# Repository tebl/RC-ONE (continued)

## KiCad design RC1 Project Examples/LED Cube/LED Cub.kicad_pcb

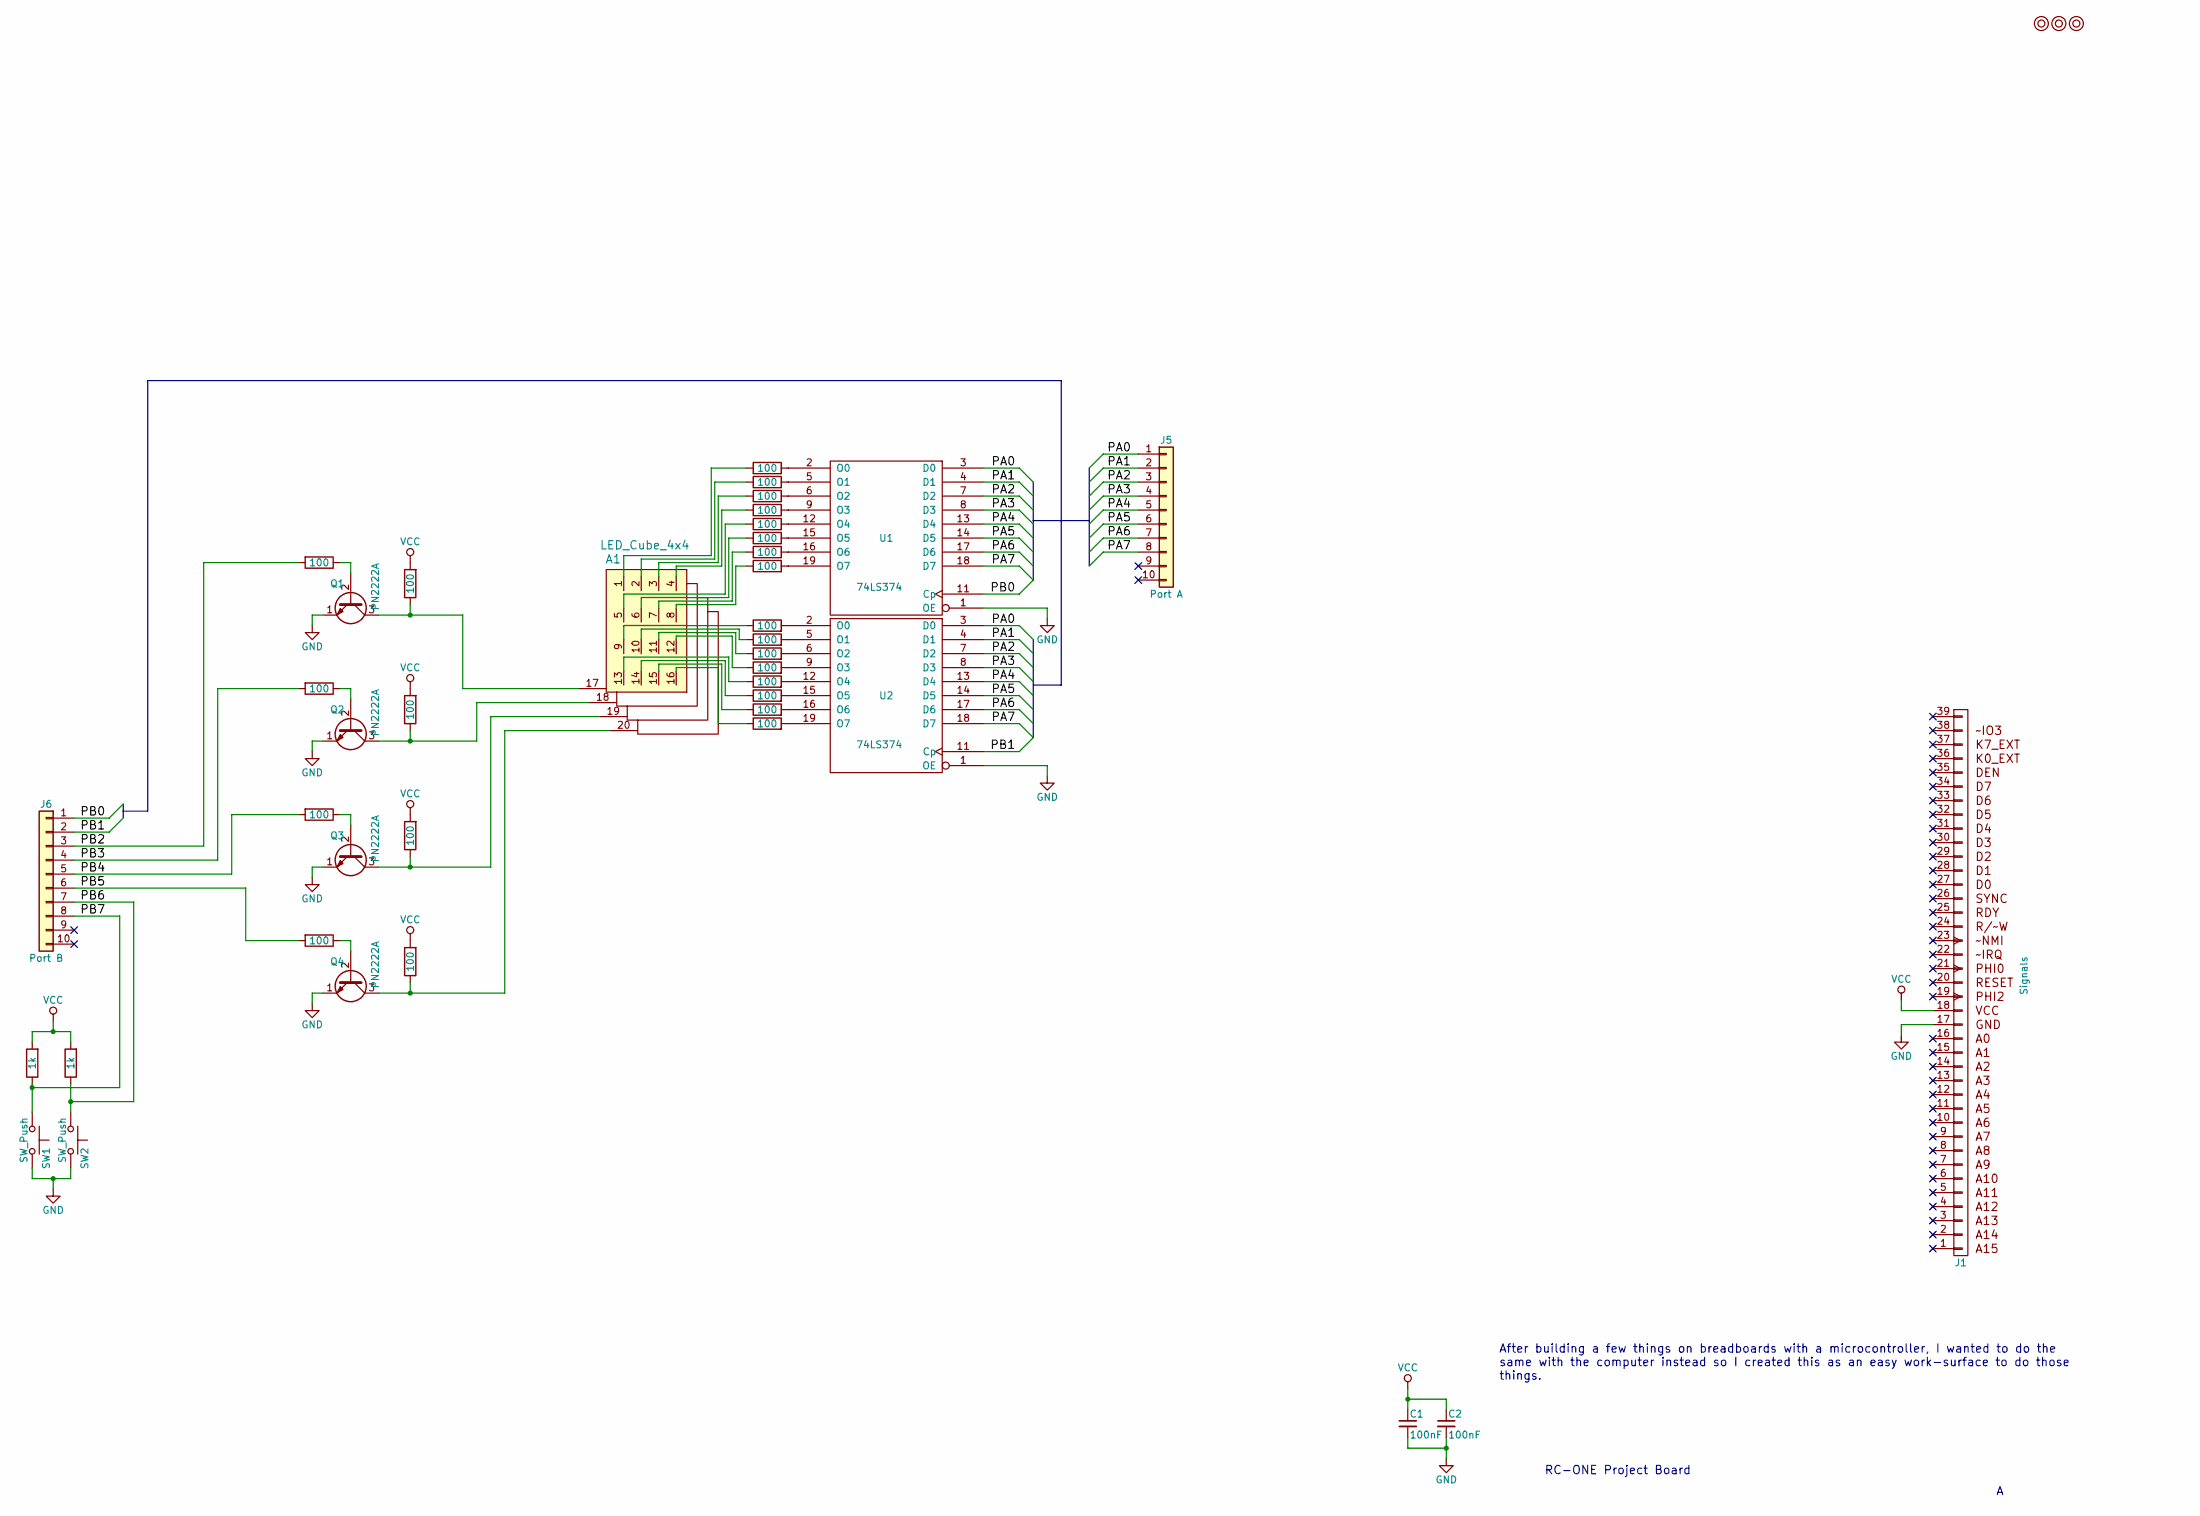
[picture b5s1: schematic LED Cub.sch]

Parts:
A1: LED_Cube_4x4
C1, C2: 100nF; C_Disc_D4.7mm_W2.5mm_P5.00mm
J1: Signals; Pin_Header_Straight_1x39_Pitch2.54mm
J5: Port A; Pin_Header_Straight_1x10_Pitch2.54mm
J6: Port B; Pin_Header_Straight_1x10_Pitch2.54mm
M1, M2, M3: Mounting; 1pin
Q1, Q2, Q3, Q4: PN2222A; TO-92_Molded_Narrow
R1, R2, R3, R4, R5, R6, R7, R8, R9, R10, R11, R12, R15, R16, R17, R18, R19, R20, R21, R22, R23, R24, R25, R26: 100; R_Axial_DIN0207_L6.3mm_D2.5mm_P10.16mm_Horizontal
R13, R14: 1k; R_Axial_DIN0207_L6.3mm_D2.5mm_P10.16mm_Horizontal
SW1, SW2: SW_Push; SW_PUSH_6mm
U1, U2: 74LS374; DIP-20_W7.62mm_Socket_LongPads

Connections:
/PA0: J5.1, U1.3 (D0), U2.3 (D0)
/PA1: J5.2, U1.4 (D1), U2.4 (D1)
/PA2: J5.3, U1.7 (D2), U2.7 (D2)
/PA3: J5.4, U1.8 (D3), U2.8 (D3)
/PA4: J5.5, U1.13 (D4), U2.13 (D4)
/PA5: J5.6, U1.14 (D5), U2.14 (D5)
/PA6: J5.7, U1.17 (D6), U2.17 (D6)
/PA7: J5.8, U1.18 (D7), U2.18 (D7)
/PB0: J6.1, U1.11 (Cp)
/PB1: J6.2, U2.11 (Cp)
/PB2: J6.3, R1.2
/PB3: J6.4, R2.2
/PB4: J6.5, R3.2
/PB5: J6.6, R4.2
/PB6: J6.7, R14.1, SW2.1
/PB7: J6.8, R13.1, SW1.1
GND: C1.2, C2.2, J1.17, Q1.1 (E), Q2.1 (E), Q3.1 (E), Q4.1 (E), SW1.2, SW2.2, U1.1 (OE), U1.10 (GND), U2.1 (OE), U2.10 (GND)
unnamed: A1.1 (la1), R8.1
unnamed: A1.2 (la2), R10.1
unnamed: A1.3 (la3), R11.1
unnamed: A1.4 (la4), R12.1
unnamed: A1.5 (la5), R15.1
unnamed: A1.6 (la6), R16.1
unnamed: A1.7 (la7), R17.1
unnamed: A1.8 (la8), R18.1
unnamed: A1.9 (la9), R19.1
unnamed: A1.10 (la10), R20.1
unnamed: A1.11 (la11), R21.1
unnamed: A1.12 (la12), R22.1
unnamed: A1.13 (la13), R23.1
unnamed: A1.14 (la14), R24.1
unnamed: A1.15 (la15), R25.1
unnamed: A1.16 (la16), R26.1
unnamed: A1.17 (layer0), Q1.3 (C), R9.1
unnamed: A1.18 (layer1), Q2.3 (C), R5.1
unnamed: A1.19 (layer2), Q3.3 (C), R6.1
unnamed: A1.20 (layer3), Q4.3 (C), R7.1
unnamed: Q1.2 (B), R1.1
unnamed: Q2.2 (B), R2.1
unnamed: Q3.2 (B), R3.1
unnamed: Q4.2 (B), R4.1
unnamed: R8.2, U1.2 (O0)
unnamed: R10.2, U1.5 (O1)
unnamed: R11.2, U1.6 (O2)
unnamed: R12.2, U1.9 (O3)
unnamed: R15.2, U1.12 (O4)
unnamed: R16.2, U1.15 (O5)
unnamed: R17.2, U1.16 (O6)
unnamed: R18.2, U1.19 (O7)
unnamed: R19.2, U2.2 (O0)
unnamed: R20.2, U2.5 (O1)
unnamed: R21.2, U2.6 (O2)
unnamed: R22.2, U2.9 (O3)
unnamed: R23.2, U2.12 (O4)
unnamed: R24.2, U2.15 (O5)
unnamed: R25.2, U2.16 (O6)
unnamed: R26.2, U2.19 (O7)
VCC: C1.1, C2.1, J1.18, R5.2, R6.2, R7.2, R9.2, R13.2, R14.2, U1.20 (VCC), U2.20 (VCC)

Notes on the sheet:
RC-ONE Project Board
After building a few things on breadboards with a microcontroller, I wanted to do the same with the computer instead so I created this as an easy work-surface to do those things.

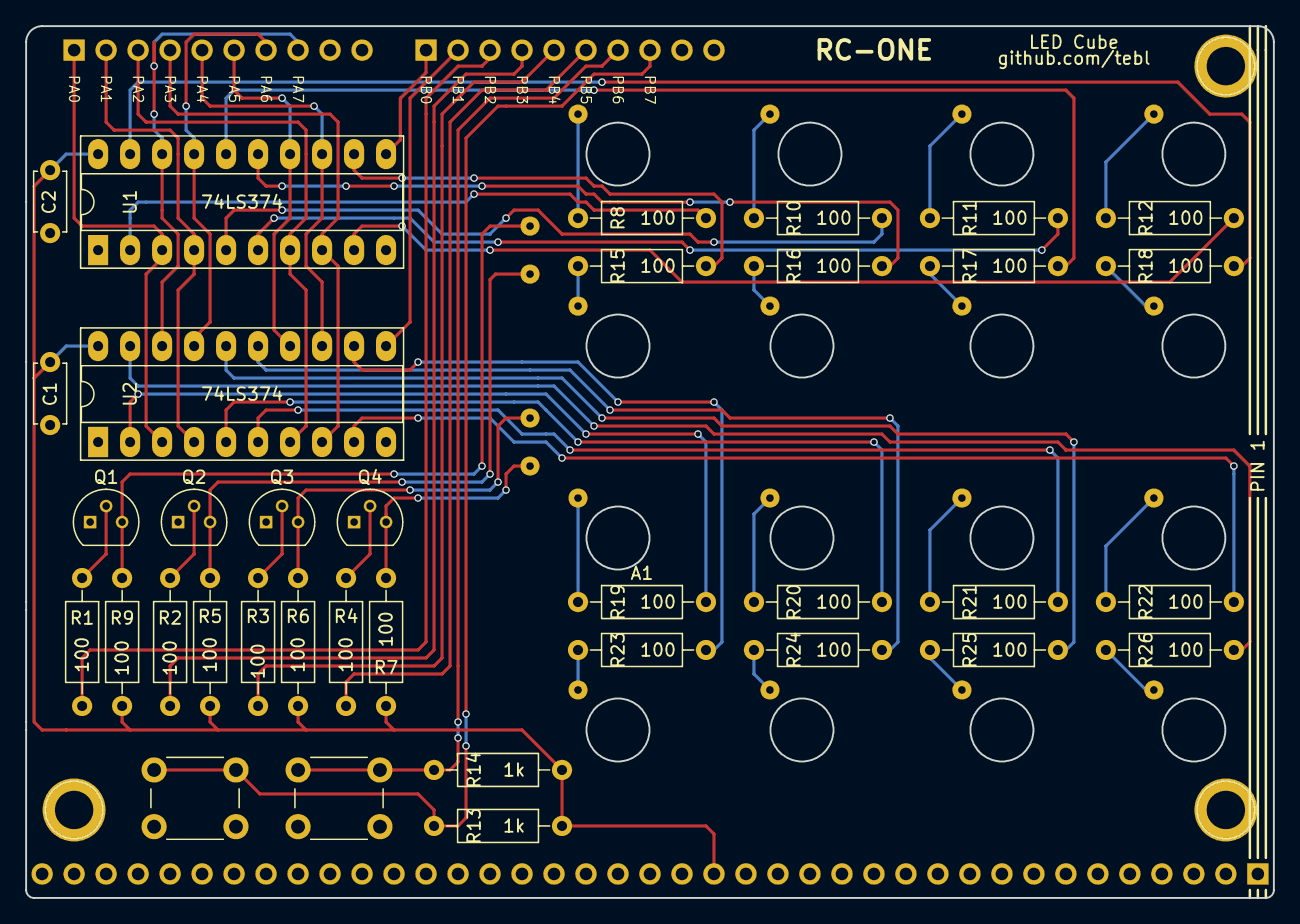
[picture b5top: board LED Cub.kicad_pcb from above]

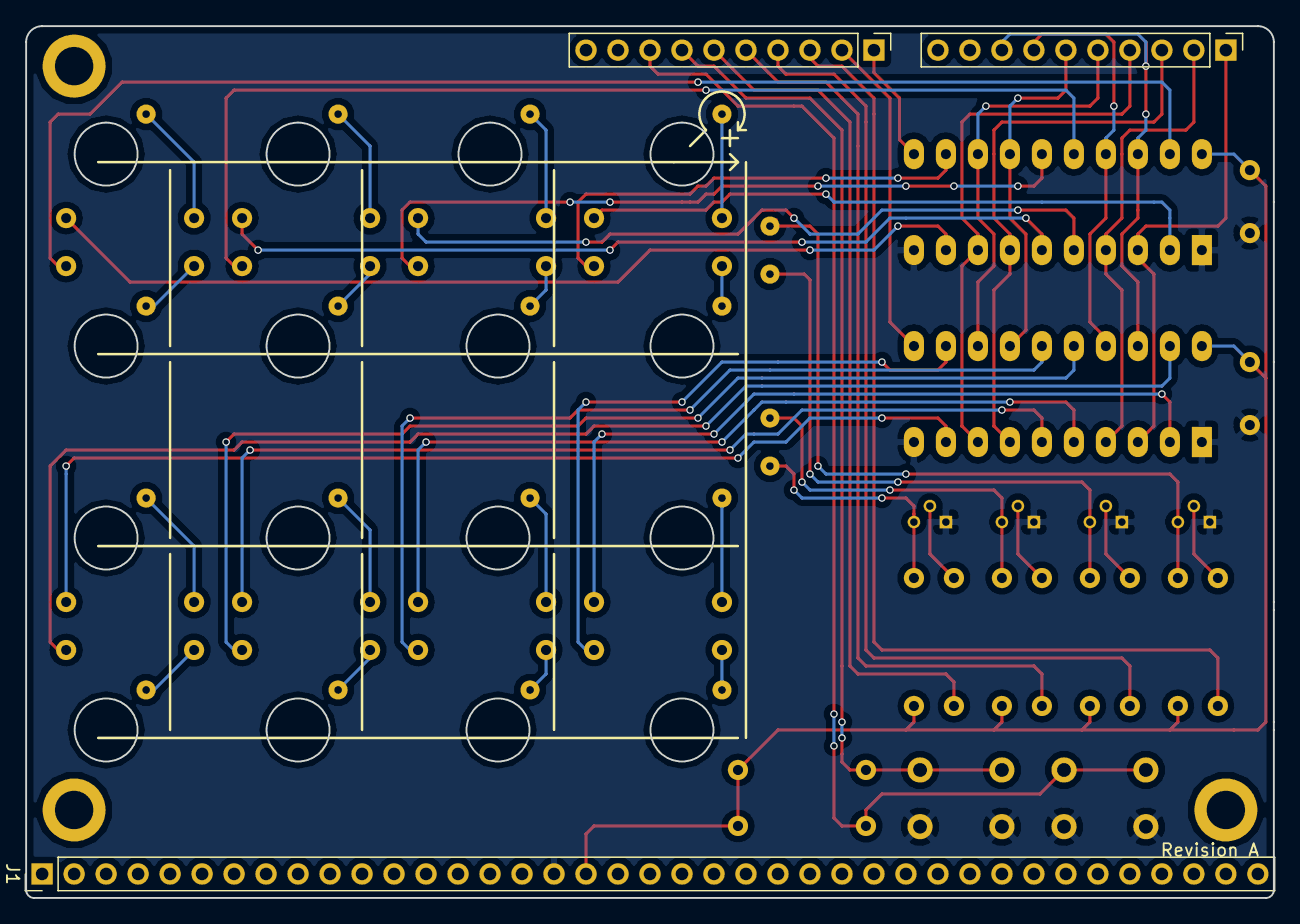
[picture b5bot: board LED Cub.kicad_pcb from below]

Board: 2 copper layers, 99.1 x 69.2 mm, 43 parts (3 on the bottom side), 58 nets.

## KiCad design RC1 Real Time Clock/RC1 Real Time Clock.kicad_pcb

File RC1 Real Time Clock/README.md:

# RC-ONE Real Time Clock (RTC)

**This design is untested!**

Wanted a Real Time Clock, but have been a hard time locating a suitable circuit for it since most of them either contain batteries that ran out a decade ago or are based on I2C or SPI (which I don't feel like bit-banging now or possibly ever). Appearantly there is a chip called DS12885 that is suitable and was readily used on the XT and AT line of computers, so they are cheap and plentiful though have a multi-plexed bus that is probably why it haven't been much used for SBC builds. Did however find an article in [Elektor Electronics from april 1985](https://www.americanradiohistory.com/UK/Elektor/80s/Elektor-1985-04.pdf) that uses it, so I've tried my best to adapt it for use here.

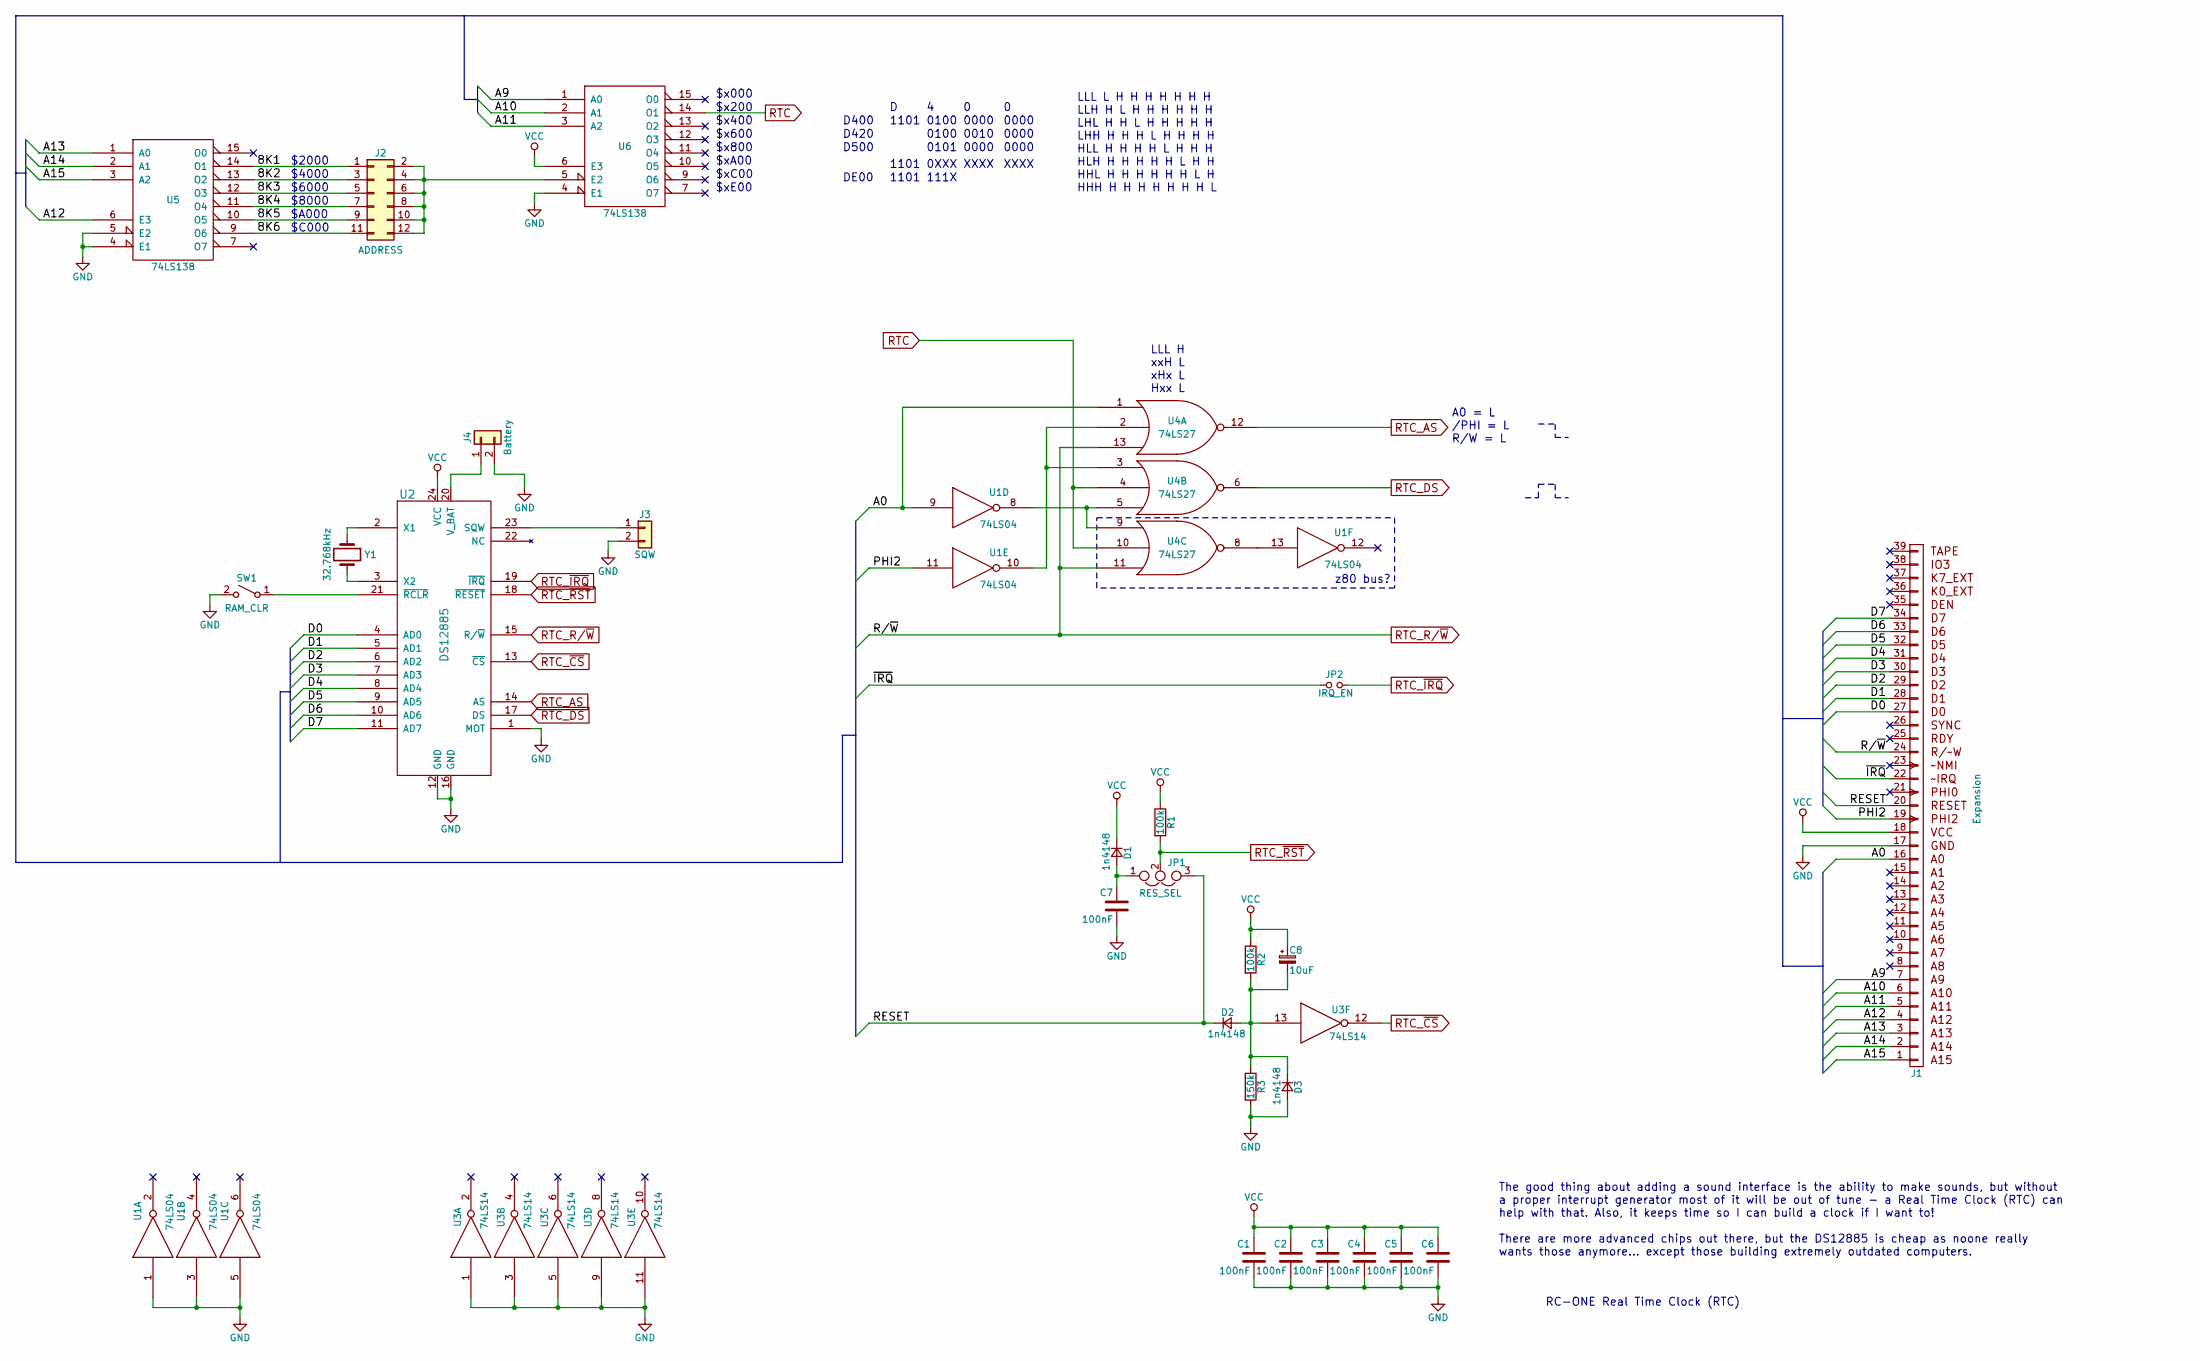
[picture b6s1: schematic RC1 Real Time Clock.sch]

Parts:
C1, C2, C3, C4, C5, C6, C7: 100nF; C_Disc_D4.7mm_W2.5mm_P5.00mm
C8: 10uF; CP_Radial_D5.0mm_P2.50mm
D1, D2, D3: 1n4148; D_DO-35_SOD27_P7.62mm_Horizontal
J1: Expansion; Pin_Header_Angled_1x39_Pitch2.54mm
J2: ADDRESS; Pin_Header_Straight_2x06_Pitch2.54mm
J3: SQW; Pin_Header_Straight_1x02_Pitch2.54mm
J4: Battery; Pin_Header_Straight_1x02_Pitch2.54mm
JP1: RES_SEL; Pin_Header_Straight_1x03_Pitch2.54mm
JP2: IRQ_EN; Pin_Header_Straight_1x02_Pitch2.54mm
R1, R2: 100k; R_Axial_DIN0207_L6.3mm_D2.5mm_P10.16mm_Horizontal
R3: 150k; R_Axial_DIN0207_L6.3mm_D2.5mm_P10.16mm_Horizontal
SW1: RAM_CLR; SW_PUSH_6mm
U1: 74LS04; DIP-14_W7.62mm_Socket
U2: DS12885; DIP-24_W15.24mm_Socket
U3: 74LS14; DIP-14_W7.62mm_Socket
U4: 74LS27; DIP-14_W7.62mm_Socket
U5, U6: 74LS138; DIP-16_W7.62mm_Socket
Y1: 32.768kHz; Crystal_HC49-U_Vertical

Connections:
/8K1: J2.1, U5.14 (O1)
/8K2: J2.3, U5.13 (O2)
/8K3: J2.5, U5.12 (O3)
/8K4: J2.7, U5.11 (O4)
/8K5: J2.9, U5.10 (O5)
/8K6: J2.11, U5.9 (O6)
/A0: J1.16 (A0), U1.9, U4.1
/A9: J1.7 (A9), U6.1 (A0)
/A10: J1.6 (A10), U6.2 (A1)
/A11: J1.5 (A11), U6.3 (A2)
/A12: J1.4 (A12), U5.6 (E3)
/A13: J1.3 (A13), U5.1 (A0)
/A14: J1.2 (A14), U5.2 (A1)
/A15: J1.1 (A15), U5.3 (A2)
/D0: J1.27 (D0), U2.4 (AD0)
/D1: J1.28 (D1), U2.5 (AD1)
/D2: J1.29 (D2), U2.6 (AD2)
/D3: J1.30 (D3), U2.7 (AD3)
/D4: J1.31 (D4), U2.8 (AD4)
/D5: J1.32 (D5), U2.9 (AD5)
/D6: J1.33 (D6), U2.10 (AD6)
/D7: J1.34 (D7), U2.11 (AD7)
/PHI2: J1.19 (PHI2), U1.11
/RESET: D2.1 (K), J1.20 (RESET), JP1.3
/~IRQ: J1.22 (IRQ), JP2.1
GND: C1.2, C2.2, C3.2, C4.2, C5.2, C6.2, C7.2, D3.2 (A), J1.17, J3.2, J4.2, R3.2, SW1.2 (B), U1.1, U1.3, U1.5, U1.7 (GND), U2.1 (MOT), U2.12 (GND), U2.16 (GND), U3.1, U3.3, U3.5, U3.7 (GND), U3.9, U3.11, U4.7 (GND), U5.4 (E1), U5.5 (E2), U5.8 (GND), U6.4 (E1), U6.8 (GND)
unnamed: C7.1, D1.2 (A), JP1.1
unnamed: C8.2, D2.2 (A), D3.1 (K), R2.2, R3.1, U3.13
unnamed: J2.2, J2.4, J2.6, J2.8, J2.10, J2.12, U6.5 (E2)
unnamed: J3.1, U2.23 (SQW)
unnamed: J4.1, U2.20 (V_BAT)
unnamed: SW1.1 (A), U2.21 (~RCLR)
unnamed: U1.8, U4.5, U4.9
unnamed: U1.10, U4.2, U4.3
unnamed: U1.13, U4.8
unnamed: U2.2 (X1), Y1.1
unnamed: U2.3 (X2), Y1.2
RTC: U4.4, U4.10, U6.14 (O1)
RTC_AS: U2.14 (AS), U4.12
RTC_DS: U2.17 (DS), U4.6
RTC_R/~W: J1.24 (RW), U2.15 (R/~W), U4.11, U4.13
RTC_~CS: U2.13 (~CS), U3.12
RTC_~IRQ: JP2.2, U2.19 (~IRQ)
RTC_~RST: JP1.2, R1.2, U2.18 (~RESET)
VCC: C1.1, C2.1, C3.1, C4.1, C5.1, C6.1, C8.1, D1.1 (K), J1.18, R1.1, R2.1, U1.14 (VCC), U2.24 (VCC), U3.14 (VCC), U4.14 (VCC), U5.16 (VCC), U6.6 (E3), U6.16 (VCC)

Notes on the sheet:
RC-ONE Real Time Clock (RTC)
$2000
$4000
$6000
$8000
$A000
$C000
$x000
1101
0100
0010
0000
0101
D420
D400
D500
LLL L H H H H H H H LLH H L H H H H H H LHL H H L H H H H H LHH H H H L H H H H HLL H H H H L H H H HLH H H H H H L H H HHL H H H H H H L H HHH H H H H H H H L
0XXX
XXXX
DE00
111X
$x200
$x600
$x800
$xC00
$xA00
The good thing about adding a sound interface is the ability to make sounds, but without a proper interrupt generator most of it will be out of tune - a Real Time Clock (RTC) can help with that. Also, it keeps time so I can build a clock if I want to! There are more advanced chips out there, but th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
$xE00
$x400
LLL H xxH L xHx L Hxx L
A0 = L /PHI = L R/W = L
z80 bus?

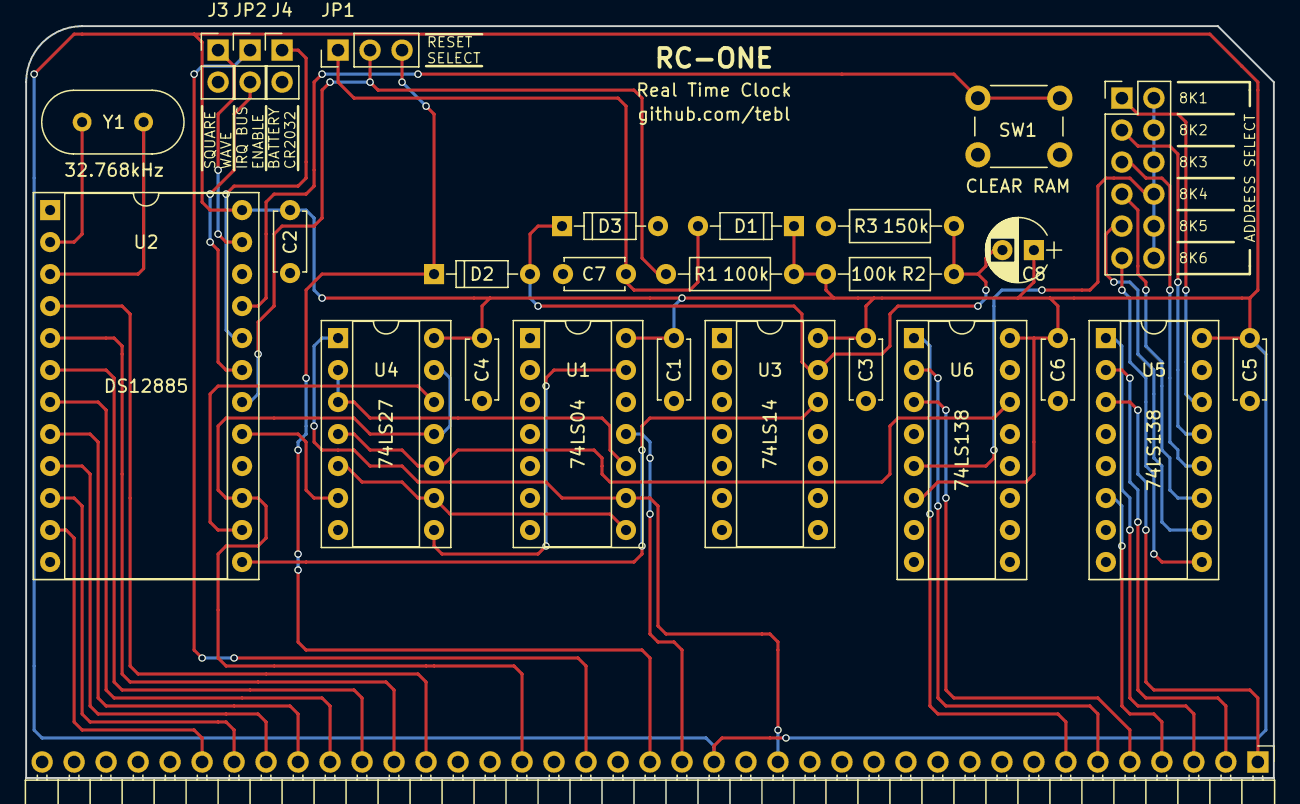
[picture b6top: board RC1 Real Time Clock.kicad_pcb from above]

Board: 2 copper layers, 99.1 x 59.7 mm, 28 parts (0 on the bottom side), 45 nets.

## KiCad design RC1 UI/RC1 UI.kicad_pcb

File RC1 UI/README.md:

# RC-ONE

Among the years I've built quite a few computers, some bought as kits from various vendors and some I even designed myself based on available designs describes in books and other technical resources - above all, there was one I really wanted above all of them; the KIM-1! The [RC-ONE](https://github.com/tebl/RC-ONE) is a functional replica designed in a modular fashion, for the specifics see the specific module.

## User Interface (UI)
The *User Interface (UI)* board has been created to stack on top of the CPU-board, see below for an indication of how that'll look on a completed revision B system - I'm using M3 nylon standoffs to support the boards.

The UI board takes care of all the various ways that the user can interact with the computer, it should functionally include all the functions found on the original computer such as 7-segment displays, keypad connector, a simplified tape interface as well as the ability to connect with a serial terminal.

The displays function the same way as the original displays, but the output hardwareas well as the logic dealing with device selection has been changed to replace some of the ICs that I could not reliably obtain - unfortunately at an increased chip-count, but that is the cost of doing increasingly outdated projects. The 6532 compared to the original 6530 IC has an extra I/O line, I've connected that up to the decimal point of the displays though the bahaviour of these is not supported by the original monitor program so I've added jumpers to enable/disable this functionality.

The tape interface was one created by Daniel Metzger and was featured in the book *22 micro-computer projects - to build, learn and learn*, I don't have an original KIM-1 so I can't compare the two though it is the only one I've seen that only use 5v (3.5mm jack has both audio in and out, I designed it for use with a ZX Spectrum +3 tape cables that people are still selling). 

The serial interface is now TTL level and is intended for use with USB TTL serial adapters, *USE_COM* must be jumpered when resetting the computer so that the computer knows to attempt communication over serial instead of using the displays/keypad. After starting up, the computer will await the receipt of the *ENTER* key in order to determine the baud rate that should be used when communicating with the terminal (-program).

## Jumpers
| Reference | Position | Description                                               |
| ----------| -------- | --------------------------------------------------------  |
| DP_EN     | 1-2      | Decimal point (DP) on displays connected to 6532 PB6 line |
|           | 2-3 *    | DP on displays disabled as original                       |
| DP4_EN    | 1-2 *    | DP on display 4 always on                                 |
|           | 2-3      | DP on display 4 connected to 6532 PB6 line                |
| SSD_EN    | 1-2 *    | Enable Seven Segment Displays (SSD)                       |
|           | 2-3      | Disable Seven Segment Displays (SSD)                      |
| TTY_MODE  | o-o      | Jumper to enable TTY-mode, disabled keypad/displays       |
| CTS - RTS | o-o *    | Shorts serial CTS to RTS to disable flow control          |
| COM_PWR   | o-o      | Jumpering allows the computer to be powered over the serial connection *INSTEAD* of connecting power to the CPU board |

\*) Marks the default jumpered positions for a standalone RC-ONE system.

# Schematic
The supplied KiCad files should be sufficient as both a schematic and as a starting point for ordering PCBs (basically you could just zip the contents of the export folder and upload that on a fabrication site), the schematic is also available in [PDF-format](https://github.com/tebl/RC-ONE/raw/master/RC1%20UI/export/RC1%20UI.pdf) so that you print it out and hang it on your office wall, excellent conversation starter at any technology-oriented business worth working at (or so I keep telling myself)!

If you require more assistance, there is also a separate [Troubleshooting](https://github.com/tebl/RC-ONE/blob/master/Troubleshooting.md) guide as part of the supplied documentation. Also make sure to have a read through the [Manual](https://github.com/tebl/RC-ONE/blob/master/Manual.md) to see if it's a *feature* instead!

# BOM
This is the part list as it stands now, most should be easy to get a hold of from your local electronic component shop though you might have to consider other sources depending on the quality of your local vendor. Values in parenthesis are optional components that might not be needed depending on what you want, here it's mostly the tape interface.

Some vendors will have the same ICs in different form factors, the ones you want will often be specified as being in the form of a DIP/PDIP package. For the pin headers, you probably won't find the exact pin count so just buy the 40 pin versions and snip off the parts you don't need.

| Reference       | Item                                  | Count |
| --------------- | ------------------------------------- | ----- |
| PCB             | Fabricate yourself using Gerber files |     1 |
| AFF1-AFF6       | 0.56" 7-segment displays (C.K.)       |     6 |
| C7,C9           | 50nF ceramic capacitor                |    (2)|
| C8              | 68nF ceramic capacitor                |    (1)|
| C1-C6           | 100nF ceramic capacitor               |     6 |
| C11             | 100nF ceramic capacitor               |    (1)|
| D4              | 5mm LED                               |    (1)|
| D1-D3           | 1N4148 small signal diode             |     3 |
| D5-D7           | 1N4148 small signal diode             |    (3)|
| J1              | 2x8 straight pin header               |     1 |
| J2              | 2x20 straight pin header              |     1 |
| J3              | 1x6 right-angle pin header            |     1 |
| J4 Audio        | 3.5mm 5pin green audio socket (PJ307) |    (1)|
| JP1,JP3         | 1x2 straight pin header               |     2 |
| JP4-JP6         | 1x3 straight pin header               |     3 |
| JP2             | 1x2 right-angle pin header            |     1 |
| Q1-Q6           | 2N3904 TO-92 transistor               |     6 |
| Q7-Q9           | 2N3904 TO-92 transistor               |    (3)|
| R7,R8,R14-R20   | 100 ohm resistor                      |     9 |
| R10             | 100 ohm resistor                      |    (1)|
| R13             | 220 ohm resistor                      |     1 |
| R22,R23,R25,R26 | 1k ohm resistor                       |     3 |
| R29-R31         | 1k ohm resistor                       |    (3)|
| R11,R33         | 1k5 (1500) ohm resistor               |    (2)|
| R36             | 2k2 (2200) ohm resistor               |    (1)|
| R27             | 2k7 (2700) ohm resistor               |    (1)|
| R32             | 6k8 (6800) ohm resistor               |    (1)|
| R1-R6,R21       | 10k ohm resistor                      |     7 |
| R9,R28,R34      | 10k ohm resistor                      |    (3)|
| R35             | 51k ohm resistor                      |    (1)|
| U1,U2           | 74LS138 (DIP-16)                      |     2 |
| U3              | 74LS01 (DIP-14) **                    |    (1)|
| U4              | 74LS00 (DIP-14)                       |     1 |
| U5              | 74LS04 (DIP-14)                       |     1 |
| U6              | 74LS244 (DIP-20)                      |     1 |
|                 | Jumpers for settings (CAP headers)    |     4 |

*) These values depend on the color of the seven segment displays you bought, 100 was a bit dim on the green displays though red ones should be good. Personally I'd bump it up a notch on the blue displays. Test on a breadboard first if the brightness is important to you, if in doubt use 100 ohm.

**) The 74LS01 is not stocked everywhere, but it seems the NTE74LS01 is still being produced. The computer will mostly function without it, but you won't be able to single-step code or use the serial interface so it's wort getting one!

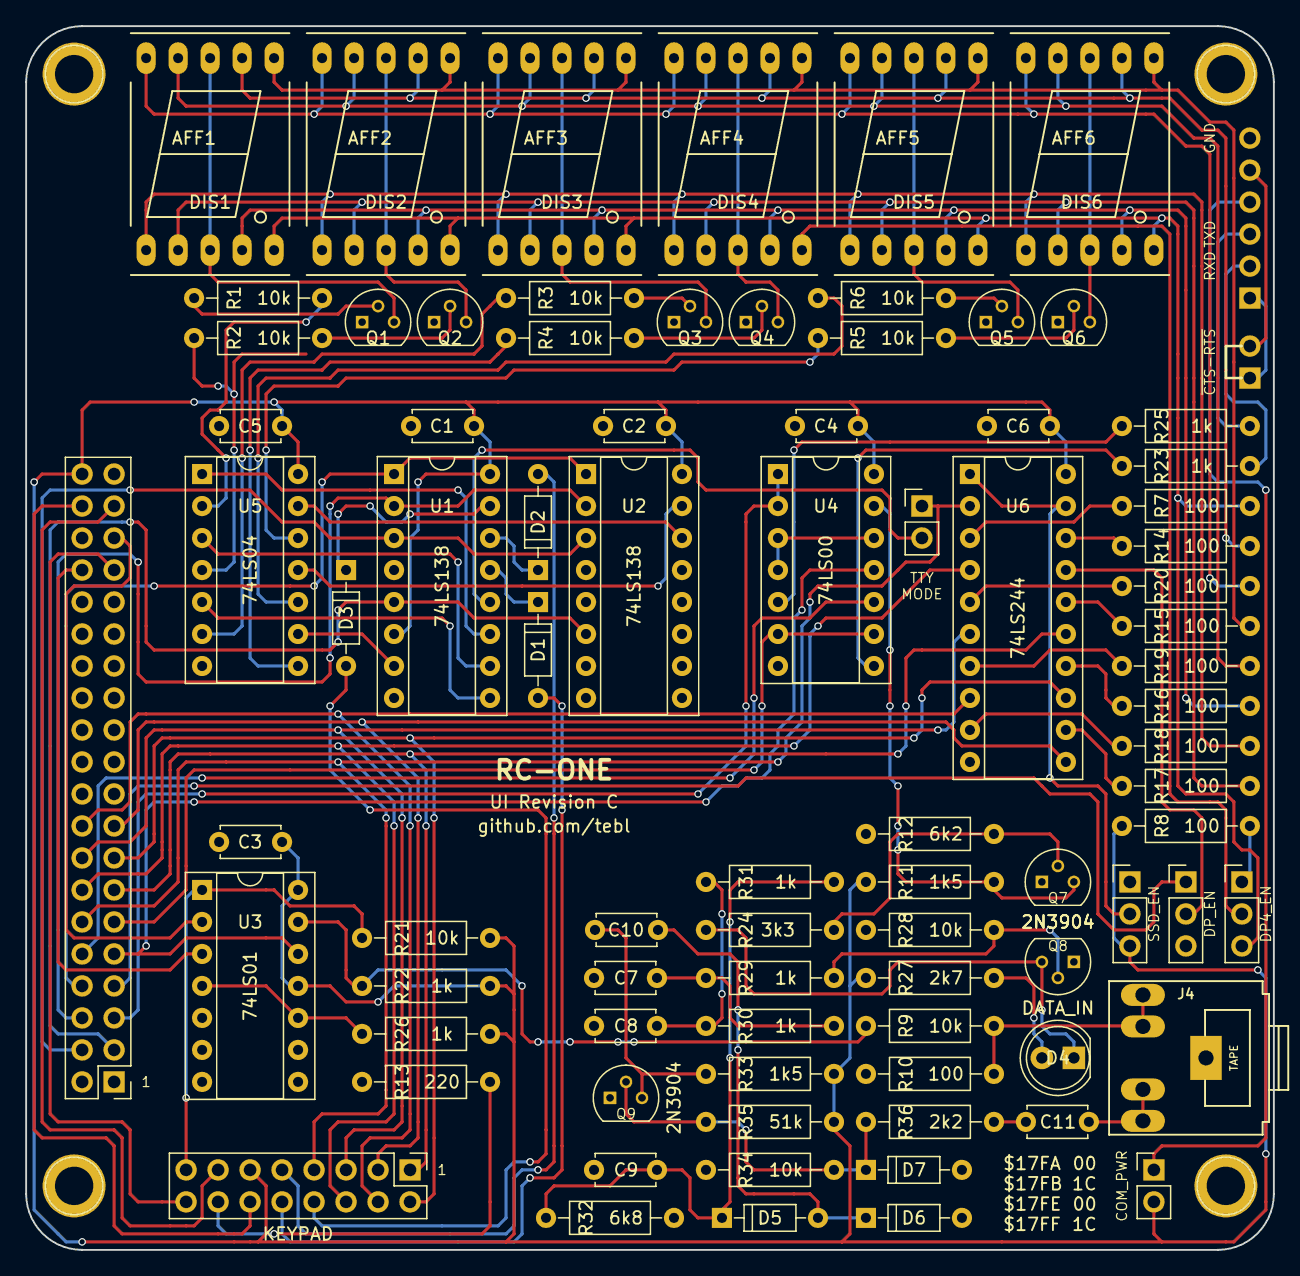
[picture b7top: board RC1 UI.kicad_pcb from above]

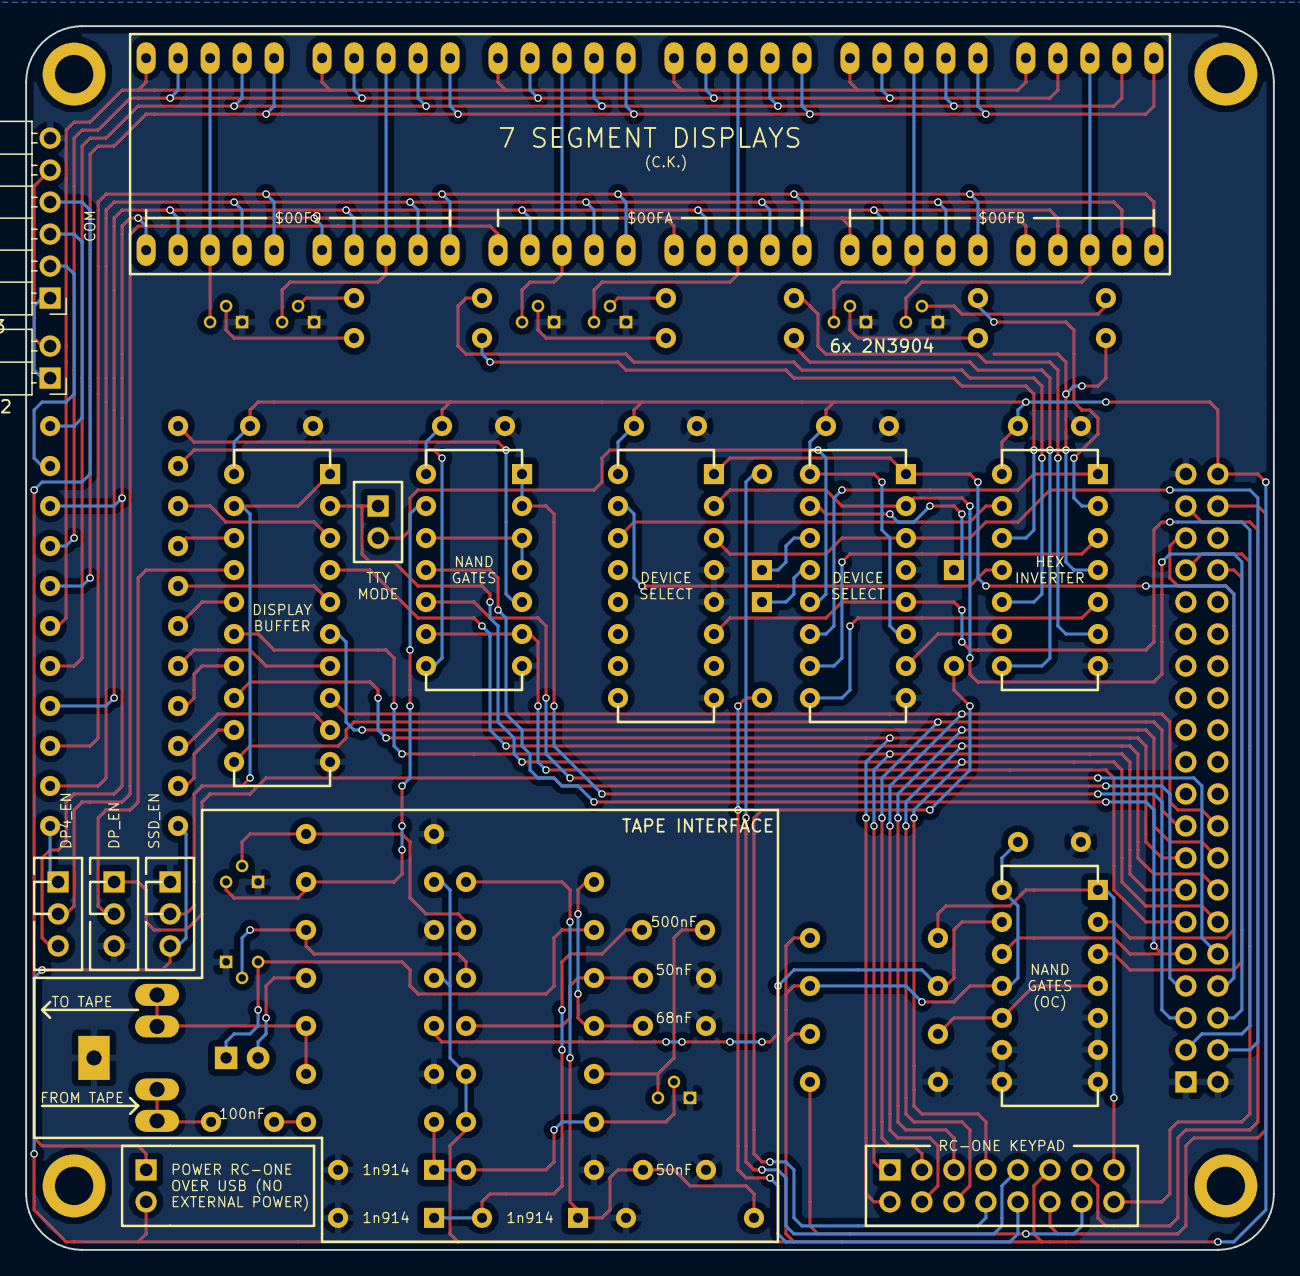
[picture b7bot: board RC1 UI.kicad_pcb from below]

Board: 2 copper layers, 99.1 x 97.2 mm, 89 parts (2 on the bottom side), 100 nets.

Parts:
AFF1: DIS1; 7SegmentLED_LTS6760_LTS6780
AFF2: DIS2; 7SegmentLED_LTS6760_LTS6780
AFF3: DIS3; 7SegmentLED_LTS6760_LTS6780
AFF4: DIS4; 7SegmentLED_LTS6760_LTS6780
AFF5: DIS5; 7SegmentLED_LTS6760_LTS6780
AFF6: DIS6; 7SegmentLED_LTS6760_LTS6780
C1, C2, C3, C4, C5, C6, C11: 100nF; C_Disc_D4.7mm_W2.5mm_P5.00mm
C7, C9: 50nF; C_Disc_D4.7mm_W2.5mm_P5.00mm
C8: 68nF; C_Disc_D4.7mm_W2.5mm_P5.00mm
C10: 500nF; C_Disc_D4.7mm_W2.5mm_P5.00mm
D1, D2, D3: 1n4148; D_DO-35_SOD27_P7.62mm_Horizontal
D4: DATA_IN; LED_D5.0mm
D5, D6, D7: 1n914; D_DO-35_SOD27_P7.62mm_Horizontal
J1: KEYPAD; Pin_Header_Straight_2x08_Pitch2.54mm
J2: RC1_UI_Port; Pin_Header_Straight_2x20_Pitch2.54mm
J3: COM; Pin_Header_Angled_1x06_Pitch2.54mm
J4: TAPE; Tayda_3.5mm_stereo_TRS_jack_A-853
JP1: COM_PWR; Pin_Header_Straight_1x02_Pitch2.54mm
JP2: FlowControl; Pin_Header_Angled_1x02_Pitch2.54mm
JP3: USE_COM; Pin_Header_Straight_1x02_Pitch2.54mm
JP4: DP_EN; Pin_Header_Straight_1x03_Pitch2.54mm
JP5: SSD_EN; Pin_Header_Straight_1x03_Pitch2.54mm
JP6: DP4_EN; Pin_Header_Straight_1x03_Pitch2.54mm
M1, M2, M3, M4: Mounting; 1pin
Q1, Q2, Q3, Q4, Q5, Q6, Q7, Q8, Q9: 2N3904; TO-92_Molded_Narrow
R1, R2, R3, R4, R5, R6, R9, R21, R28, R34: 10k; R_Axial_DIN0207_L6.3mm_D2.5mm_P10.16mm_Horizontal
R7, R8, R10, R14, R15, R16, R17, R18, R19, R20: 100; R_Axial_DIN0207_L6.3mm_D2.5mm_P10.16mm_Horizontal
R11, R33: 1k5; R_Axial_DIN0207_L6.3mm_D2.5mm_P10.16mm_Horizontal
R12: 6k2; R_Axial_DIN0207_L6.3mm_D2.5mm_P10.16mm_Horizontal
R13: 220; R_Axial_DIN0207_L6.3mm_D2.5mm_P10.16mm_Horizontal
R22, R23, R25, R26, R29, R30, R31: 1k; R_Axial_DIN0207_L6.3mm_D2.5mm_P10.16mm_Horizontal
R24: 3k3; R_Axial_DIN0207_L6.3mm_D2.5mm_P10.16mm_Horizontal
R27: 2k7; R_Axial_DIN0207_L6.3mm_D2.5mm_P10.16mm_Horizontal
R32: 6k8; R_Axial_DIN0207_L6.3mm_D2.5mm_P10.16mm_Horizontal
R35: 51k; R_Axial_DIN0207_L6.3mm_D2.5mm_P10.16mm_Horizontal
R36: 2k2; R_Axial_DIN0207_L6.3mm_D2.5mm_P10.16mm_Horizontal
U1, U2: 74LS138; DIP-16_W7.62mm_Socket
U3: 74LS01; DIP-14_W7.62mm_Socket
U4: 74LS00; DIP-14_W7.62mm_Socket
U5: 74LS04; DIP-14_W7.62mm_Socket
U6: 74LS244; DIP-20_W7.62mm_Socket

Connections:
/A: AFF1.7, AFF2.7, AFF3.7, AFF4.7, AFF5.7, AFF6.7, R14.2
/B: AFF1.6, AFF2.6, AFF3.6, AFF4.6, AFF5.6, AFF6.6, R15.2
/C: AFF1.4, AFF2.4, AFF3.4, AFF4.4, AFF5.4, AFF6.4, R16.2
/D: AFF1.2, AFF2.2, AFF3.2, AFF4.2, AFF5.2, AFF6.2, R17.2
/DIS1: R1.2, U5.2
/DIS2: R2.2, U5.4
/DIS3: R3.2, U5.6
/DIS4: R4.2, U5.8
/DIS5: R5.2, U5.10
/DIS6: R6.2, U5.12
/DP: AFF1.5, AFF2.5, AFF3.5, AFF5.5, AFF6.5, JP6.3, R7.2
/DP4: AFF4.5, JP6.2
/E: AFF1.1, AFF2.1, AFF3.1, AFF4.1, AFF5.1, AFF6.1, R18.2
/F: AFF1.9, AFF2.9, AFF3.9, AFF4.9, AFF5.9, AFF6.9, R19.2
/G: AFF1.10, AFF2.10, AFF3.10, AFF4.10, AFF5.10, AFF6.10, R20.2
/KP_RS: J1.13, J2.37
/KP_ST: J1.12, J2.38
/MODE: JP3.2, U1.12
/PA0: J1.7, J2.12, JP3.1, U6.2
/PA1: J1.6, J2.14, U6.4
/PA2: J1.5, J2.16, U6.6
/PA3: J1.4, J2.18, U6.8
/PA4: J1.3, J2.17, U6.11
/PA5: J1.2, J2.15, U6.13
/PA6: J1.1, J2.13, U6.15
/PA7: J2.11, U4.6, U4.9
/PB0: J2.10, U4.10
/PB1: J2.8, U1.1, U2.1
/PB2: J2.6, U1.2, U2.2
/PB3: J2.4, U1.3, U2.3
/PB4: J2.3, U1.5, U2.6
/PB5: J2.5, U4.1, U4.2
/PB6: J2.7, JP4.1
/PB7: J2.9, U3.12, U4.11
/ROW0: D3.2, J1.8
/ROW1: D2.2, J1.9
/ROW2: D1.2, J1.10
/RX: R25.1, U4.5
/TAPE_EAR: C11.2, J4.2, J4.3
/TAPE_MIC: J4.4, J4.5, R9.1, R10.1
/TX: R23.1, U4.8
FROM_TAPE: Q7.3, R11.1, U4.13
GND: C1.2, C2.2, C3.2, C4.2, C5.2, C6.2, C7.1, C8.1, C9.1, D6.2, D7.2, J2.1, J2.2, J2.39, J3.6, J4.1, JP4.3, JP5.1, Q1.1, Q2.1, Q3.1, Q4.1, Q5.1, Q6.1, Q7.1, Q8.1, Q9.1, R10.2, R12.2, R13.2, R28.1, R32.2, R34.2, U1.4, U1.8, U2.4, U2.5, U2.8, U3.5, U3.6, U3.7, U3.8, U3.9, U4.7, U5.7, U6.10
K7: J2.35, U3.2
unnamed: AFF1.3, AFF1.8, Q1.3
unnamed: AFF2.3, AFF2.8, Q2.3
unnamed: AFF3.3, AFF3.8, Q3.3
unnamed: AFF4.3, AFF4.8, Q4.3
unnamed: AFF5.3, AFF5.8, Q5.3
unnamed: AFF6.3, AFF6.8, Q6.3
unnamed: C7.2, R29.1, R30.2
unnamed: C8.2, R30.1, R31.2
unnamed: C9.2, D5.1, R31.1, R32.1
unnamed: C10.1, D5.2, D6.1
unnamed: C10.2, Q9.3, R33.1
unnamed: C11.1, R36.2
unnamed: D1.1, U1.13
unnamed: D2.1, U1.14
unnamed: D3.1, U1.15
unnamed: D4.1, Q8.3, R24.1
unnamed: D4.2, R27.1
unnamed: D7.1, Q9.2, R34.1, R35.2, R36.1
unnamed: J1.14, R13.1
unnamed: J3.1, JP2.1
unnamed: J3.2, R23.2
unnamed: J3.3, R25.2
unnamed: J3.4, JP1.1
unnamed: J3.5, JP2.2
unnamed: JP4.2, U6.17
unnamed: JP5.2, U6.1, U6.19
unnamed: JP6.1, R8.2
unnamed: Q1.2, R1.1
unnamed: Q2.2, R2.1
unnamed: Q3.2, R3.1
unnamed: Q4.2, R4.1
unnamed: Q5.2, R5.1
unnamed: Q6.2, R6.1
unnamed: Q7.2, R12.1, R24.2
unnamed: Q8.2, R28.2, R29.2
unnamed: R7.1, U6.3
unnamed: R14.1, U6.18
unnamed: R15.1, U6.16
unnamed: R16.1, U6.14
unnamed: R17.1, U6.12
unnamed: R18.1, U6.9
unnamed: R19.1, U6.7
unnamed: R20.1, U6.5
unnamed: R26.2, U3.4, U3.10
unnamed: U1.7, U5.9
unnamed: U1.9, U5.5
unnamed: U1.10, U5.3
unnamed: U1.11, U5.1
unnamed: U2.14, U5.13
unnamed: U2.15, U5.11
unnamed: U4.3, U4.4, U4.12
SST_IN: J1.15, R21.1, U3.1
SST_OUT: J1.16, J2.33
SYNC: J2.34, U3.3
TO_TAPE: R9.2, R22.1, U3.13
VCC: C1.1, C2.1, C3.1, C4.1, C5.1, C6.1, J1.11, J2.40, JP1.2, JP5.3, R8.1, R11.2, R21.2, R22.2, R26.1, R27.2, R33.2, R35.1, U1.6, U1.16, U2.16, U3.11, U3.14, U4.14, U5.14, U6.20
